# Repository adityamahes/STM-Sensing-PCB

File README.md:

# First PCB Project
Used Phil's Lab's tutorial as the base and built overtop

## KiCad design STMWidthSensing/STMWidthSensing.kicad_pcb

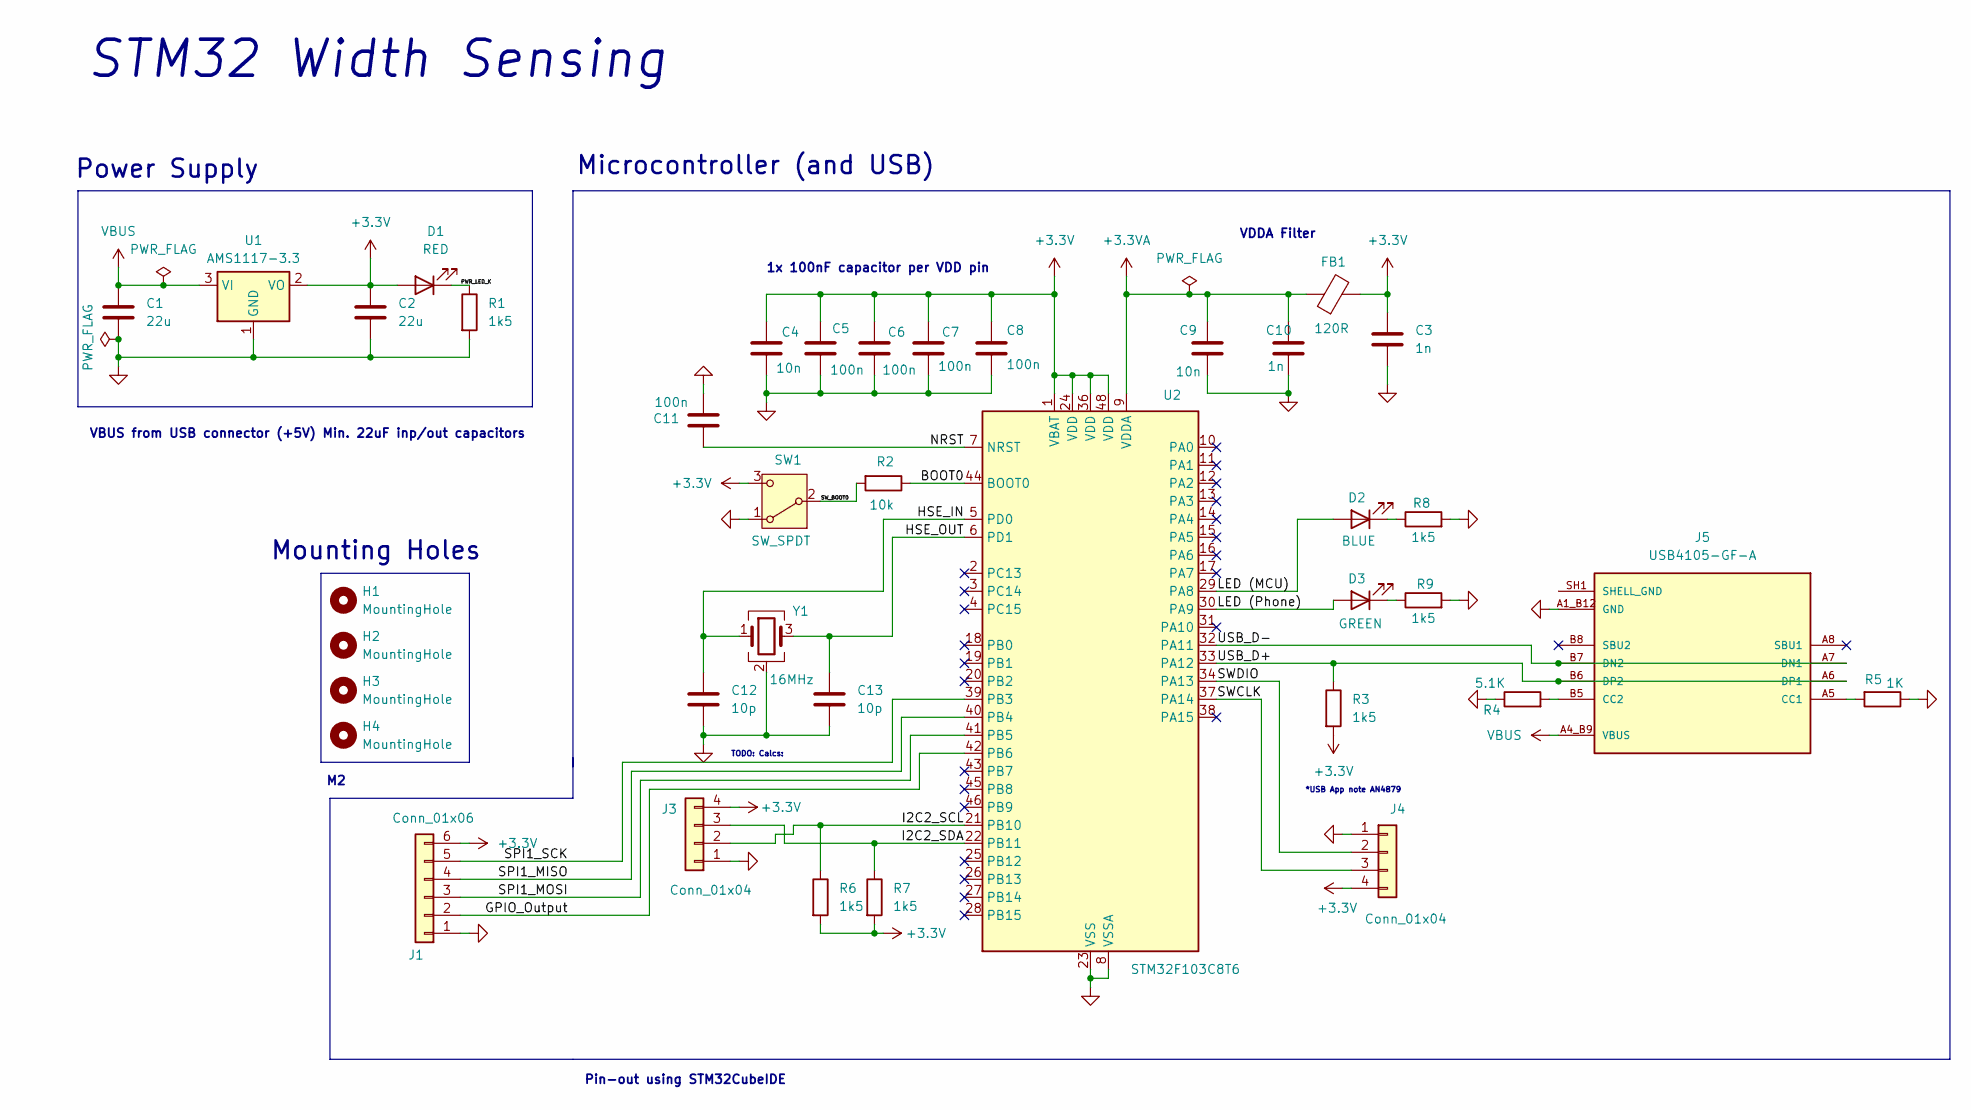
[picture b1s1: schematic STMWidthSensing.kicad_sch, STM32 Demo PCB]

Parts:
C1, C2: 22u; C_0805_2012Metric
C3, C10: 1n; C_0402_1005Metric
C4: 10n; C_0603_1608Metric
C5, C6, C7, C8, C11: 100n; C_0402_1005Metric
C9: 10n; C_0402_1005Metric
C12, C13: 10p; C_0402_1005Metric
D1: RED; LED_0603_1608Metric
D2: BLUE; LED_0603_1608Metric
D3: GREEN; LED_0603_1608Metric
FB1: 120R; L_0603_1608Metric
H1, H2, H3, H4: MountingHole; MountingHole_2.2mm_M2
J1: Conn_01x06; PinHeader_1x06_P2.54mm_Vertical
J3, J4: Conn_01x04; PinHeader_1x04_P2.54mm_Vertical
J5: USB4105-GF-A; GCT_USB4105-GF-A; PARTREV B4
R1, R3, R6, R7, R8, R9: 1k5; R_0402_1005Metric
R2: 10k; R_0402_1005Metric
R4: 5.1K; R_0402_1005Metric
R5: 1K; R_0402_1005Metric
SW1: SW_SPDT; SW_SPDT_PCM12
U1: AMS1117-3.3; SOT-223-3_TabPin2
U2: STM32F103C8T6; LQFP-48_7x7mm_P0.5mm
Y1: 16MHz; Crystal_SMD_3225-4Pin_3.2x2.5mm

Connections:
+3.3V: C2.1, C3.1, C4.1, C5.1, C6.1, C7.1, C8.1, D1.2 (A), FB1.2, J1.6, J3.4, J4.4, R3.2, R6.2, R7.2, SW1.3 (C), U1.2 (VO), U2.1 (VBAT), U2.24 (VDD), U2.36 (VDD), U2.48 (VDD)
+3.3VA: C9.1, C10.1, FB1.1, U2.9 (VDDA)
/BOOT0: R2.1, U2.44 (BOOT0)
/GPIO_Output: J1.2, U2.42 (PB6)
/HSE_IN: C12.1, U2.5 (PD0), Y1.1
/HSE_OUT: C13.1, U2.6 (PD1), Y1.3
/I2C2_SCL: J3.2, R6.1, U2.21 (PB10)
/I2C2_SDA: J3.3, R7.1, U2.22 (PB11)
/LED (MCU): D2.2 (A), U2.29 (PA8)
/LED (Phone): D3.2 (A), U2.30 (PA9)
/NRST: C11.1, U2.7 (NRST)
/PWR_LED_K: D1.1 (K), R1.1
/SPI1_MISO: J1.4, U2.40 (PB4)
/SPI1_MOSI: J1.3, U2.41 (PB5)
/SPI1_SCK: J1.5, U2.39 (PB3)
/SWCLK: J4.3, U2.37 (PA14)
/SWDIO: J4.2, U2.34 (PA13)
/SW_BOOT0: R2.2, SW1.2 (B)
/USB_D+: J5.A6 (DP1), J5.B6 (DP2), R3.1, U2.33 (PA12)
/USB_D-: J5.A7 (DN1), J5.B7 (DN2), U2.32 (PA11)
GND: C1.2, C2.2, C3.2, C4.2, C5.2, C6.2, C7.2, C8.2, C9.2, C10.2, C11.2, C12.2, C13.2, J1.1, J3.1, J4.1, J5.A1_B12 (GND), J5.B1_A12 (GND), R1.2, R4.1, R5.1, R8.2, R9.2, SW1.1 (A), U1.1 (GND), U2.8 (VSSA), U2.23 (VSS), U2.35 (VSS), U2.47 (VSS), Y1.2 (G), Y1.4 (G)
unnamed: D2.1 (K), R8.1
unnamed: D3.1 (K), R9.1
unnamed: J5.A5 (CC1), R5.2
unnamed: J5.B5 (CC2), R4.2
SHELL_GND: J5.SH1 (SHELL_GND), J5.SH2 (SHELL_GND), J5.SH3 (SHELL_GND), J5.SH4 (SHELL_GND)
VBUS: C1.1, J5.A4_B9 (VBUS), J5.B4_A9 (VBUS), U1.3 (VI)

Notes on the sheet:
1x 100nF capacitor per VDD pin
Microcontroller (and USB)
Pin-out using STM32CubeIDE
Mounting Holes
*USB App note AN4879
TODO: Calcs:
VDDA Filter
STM32 Width Sensing
Power Supply
VBUS from USB connector (+5V) Min. 22uF inp/out capacitors

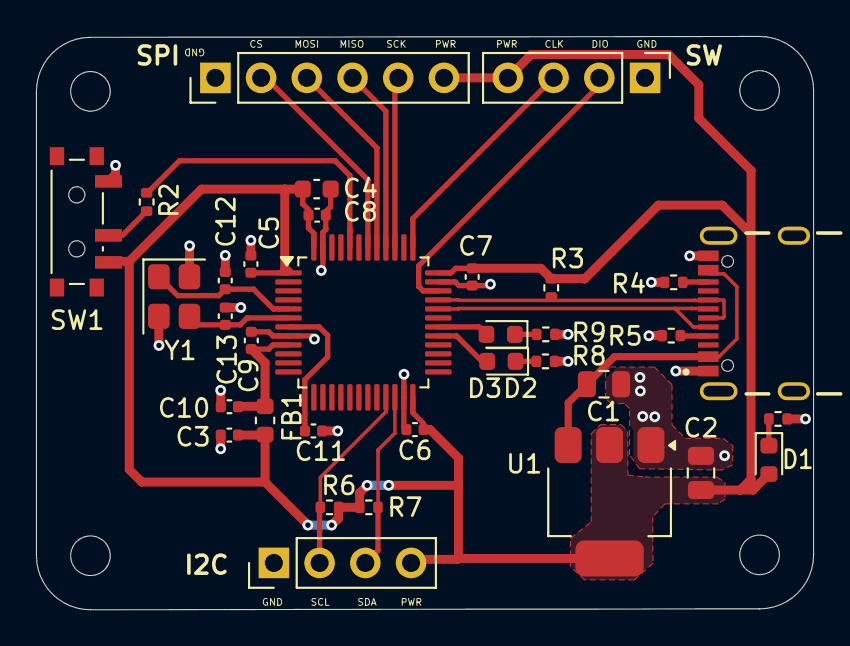
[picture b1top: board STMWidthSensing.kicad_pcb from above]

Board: 2 copper layers, 43.2 x 31.8 mm, 38 parts (0 on the bottom side), 27 nets.

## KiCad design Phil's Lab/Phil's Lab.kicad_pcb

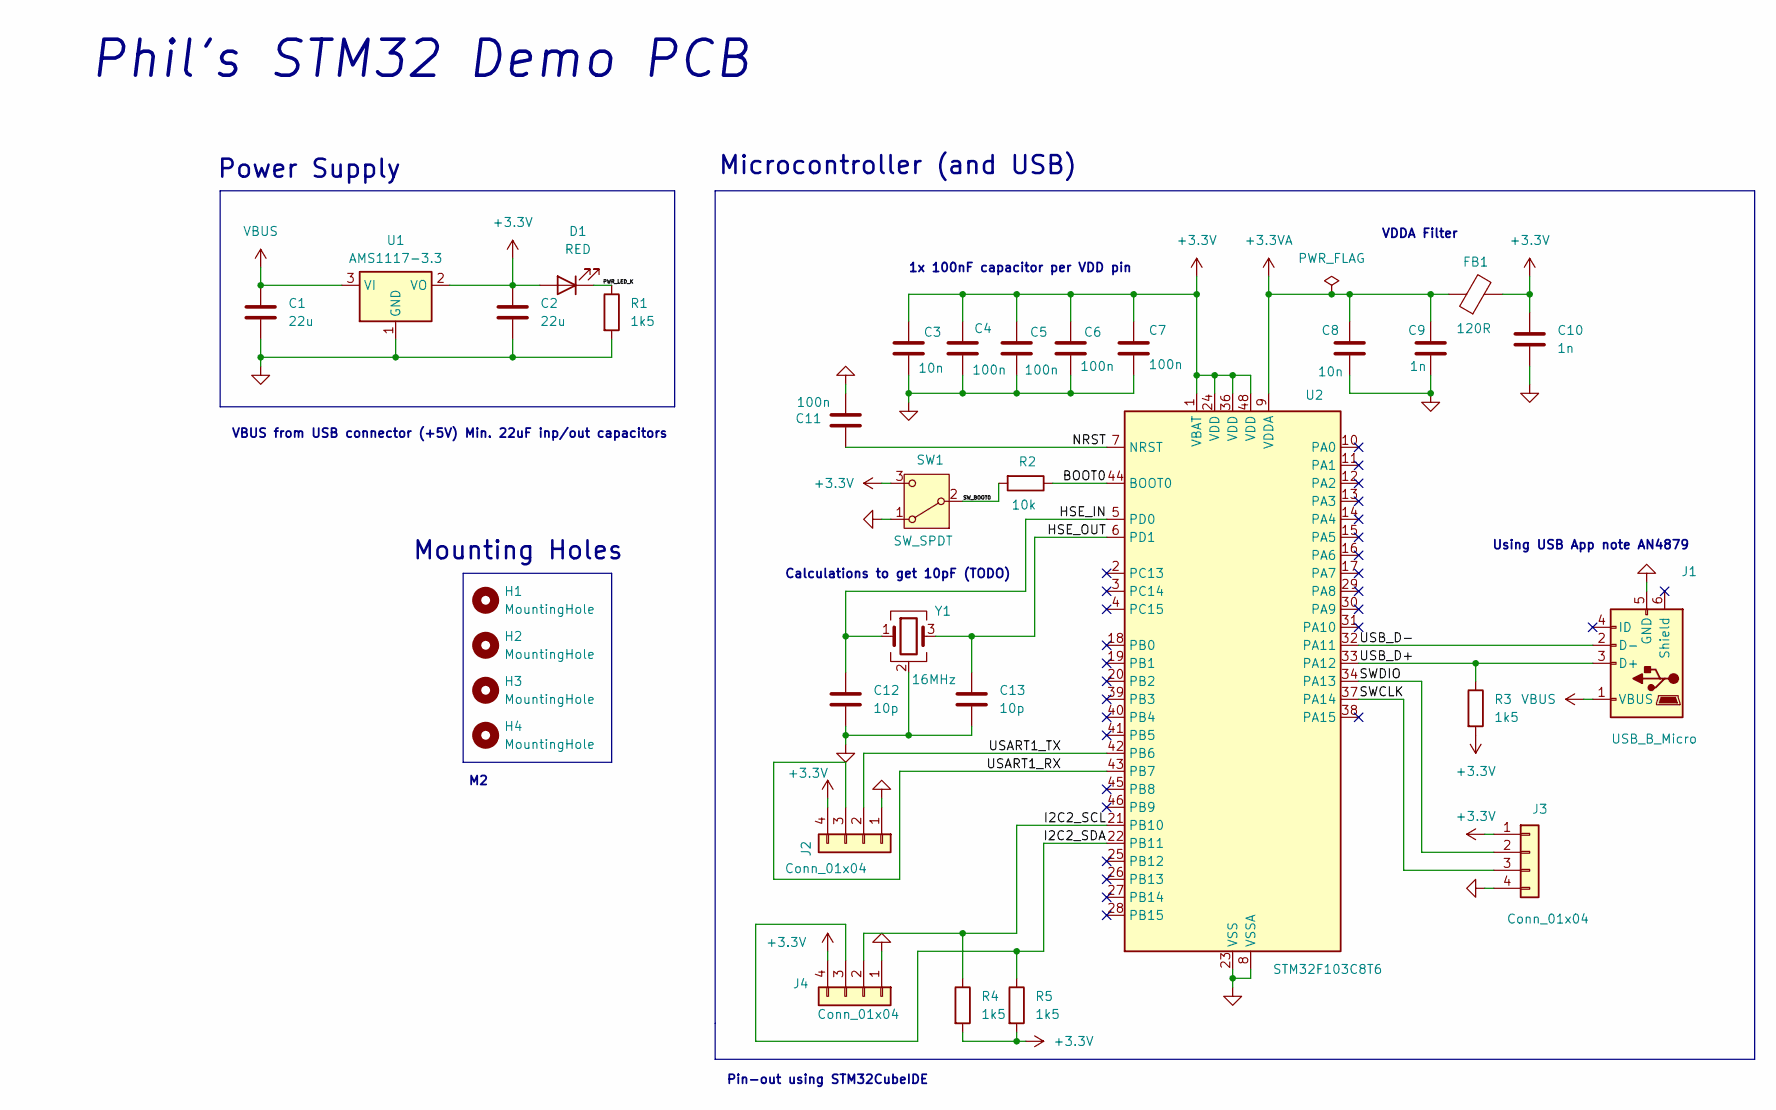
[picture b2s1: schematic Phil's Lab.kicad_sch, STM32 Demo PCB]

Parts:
C1, C2: 22u; C_0805_2012Metric
C3: 10n; C_0603_1608Metric
C4, C5, C6, C7, C11: 100n; C_0402_1005Metric
C8: 10n; C_0402_1005Metric
C9, C10: 1n; C_0402_1005Metric
C12, C13: 10p; C_0402_1005Metric
D1: RED; LED_0603_1608Metric
FB1: 120R; L_0603_1608Metric
H1, H2, H3, H4: MountingHole; MountingHole_2.2mm_M2
J1: USB_B_Micro; USB_Micro-B_Molex-105133-0031
J2, J3, J4: Conn_01x04; PinHeader_1x04_P2.54mm_Vertical
R1, R3, R4, R5: 1k5; R_0402_1005Metric
R2: 10k; R_0402_1005Metric
SW1: SW_SPDT; SW_SPDT_PCM12
U1: AMS1117-3.3; SOT-223-3_TabPin2
U2: STM32F103C8T6; LQFP-48_7x7mm_P0.5mm
Y1: 16MHz; Crystal_SMD_3225-4Pin_3.2x2.5mm

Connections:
+3.3V: C2.1, C3.1, C4.1, C5.1, C6.1, C7.1, C10.1, D1.2 (A), FB1.2, J2.4, J3.1, J4.4, R3.2, R4.2, R5.2, SW1.3 (C), U1.2 (VO), U2.1 (VBAT), U2.24 (VDD), U2.36 (VDD), U2.48 (VDD)
+3.3VA: C8.1, C9.1, FB1.1, U2.9 (VDDA)
/BOOT0: R2.1, U2.44 (BOOT0)
/HSE_IN: C12.1, U2.5 (PD0), Y1.1
/HSE_OUT: C13.1, U2.6 (PD1), Y1.3
/I2C2_SCL: J4.2, R4.1, U2.21 (PB10)
/I2C2_SDA: J4.3, R5.1, U2.22 (PB11)
/NRST: C11.1, U2.7 (NRST)
/PWR_LED_K: D1.1 (K), R1.1
/SWCLK: J3.3, U2.37 (PA14)
/SWDIO: J3.2, U2.34 (PA13)
/SW_BOOT0: R2.2, SW1.2 (B)
/USART1_RX: J2.3, U2.43 (PB7)
/USART1_TX: J2.2, U2.42 (PB6)
/USB_D+: J1.3 (D+), R3.1, U2.33 (PA12)
/USB_D-: J1.2 (D-), U2.32 (PA11)
GND: C1.2, C2.2, C3.2, C4.2, C5.2, C6.2, C7.2, C8.2, C9.2, C10.2, C11.2, C12.2, C13.2, J1.5 (GND), J2.1, J3.4, J4.1, R1.2, SW1.1 (A), U1.1 (GND), U2.8 (VSSA), U2.23 (VSS), U2.35 (VSS), U2.47 (VSS), Y1.2 (G), Y1.4 (G)
VBUS: C1.1, J1.1 (VBUS), U1.3 (VI)

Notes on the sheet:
1x 100nF capacitor per VDD pin
Microcontroller (and USB)
Pin-out using STM32CubeIDE
Mounting Holes
Using USB App note AN4879
Calculations to get 10pF (TODO)
VDDA Filter
Phil's STM32 Demo PCB
Power Supply
VBUS from USB connector (+5V) Min. 22uF inp/out capacitors

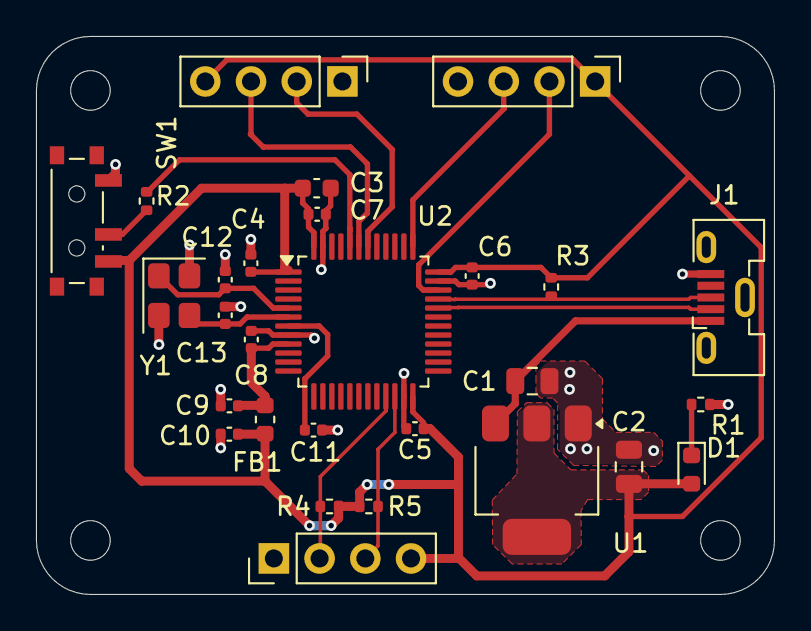
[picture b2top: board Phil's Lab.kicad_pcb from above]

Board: 2 copper layers, 41.0 x 31.0 mm, 32 parts (0 on the bottom side), 18 nets.

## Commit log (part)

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2026-06-14 Replace backup zip with newer 2026-06-14 file
    Refresh
2026-06-15 Adjust PCB footprints, add routing and backups
    Apply multiple footprint refinements and add routing: updated many component positions, pad rotations and silk/text coordinates (and several UUID updates) in Phil's Lab.kicad_pcb; added extensive F.C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
2026-06-16 Small Update
2026-06-17 USB-C added; SPI Comm added, UART Removed, 2 new LEDs to signal status
2026-06-18 Schematic: reposition nets, add wires, update symbols
    Update STMWidthSensing schematic: moved several junctions and adjusted wire routing (new/updated wires and junction UUIDs), removed a duplicate junction, and added small wiring segments to clean up n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
